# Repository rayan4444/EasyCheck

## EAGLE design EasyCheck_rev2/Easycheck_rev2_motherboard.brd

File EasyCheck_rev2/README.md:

# Easy Check rev 2
## Overview
This version includes bug fixes from the previous iteration and is designed to fit in the prototype, made for HAX Xi'an Demo Day 2019. The design has 4 boards:
* A motherboard: power circuit, MCU (ATSAMD21G), control for heater, fans and servo.
* A connection board for testing chips: ADC, chip connectors
* An Interface board: LCD screen, buzzer, 4 buttons, power LED
* Test chip boards: Serial number IC, contacts for sensing paper, power LED, NTC (temperature sensing)

## Programming
To set up the programming environment, follow the same steps as rev1.

**ATTENTION!**

To run all code properly some modification to the original board definition files from ARDUINO and 3rd party libraries are necessary: the modified files are available in this repository in the /Board Definition and /Libraries used folders.

## Errata
- I2C bus: change R11 and R14 from 4.7k to 2.2k
- The design doesn't account for a battery to keep the RTC powered on. Time gets reset to a user specified date and time at every reboot.

**Note**: the 2019/07/12 prototype uses a slightly different version of the PCB with connection errors that have ALREADY BEEN CORRECTED in the files in this repository
## Recommendations for future designs:

###### Hardware:
- To implement stackable drawers system: consider having a small microcontroller on each connection board that handles serial communication with the motherboard through RS485. you can then daisy chain the drawers as you stack them. The microcontroller on the drawer board can also handle reading the ADC and serial numbers.
- Accommodating to new test papers: move the resistor divider to the chip PCB, so you can customize it for new types of sensing papers with different resistances.

- This design uses an 8W heater, which makes the heating up process slow. Use a more powerful heater to get the system to reach 37 degrees faster. However, make sure the current consumption is within the limits of your power supply.
- Data: consider having some sort of connectivity (Wifi/ethernet) to export data and update the RTC clock.

###### Firmware:
- Scaling of the x-axis in the LCD diplay temperature plot according to test duration
- Improve temperature PID controller by tuning Ki, Kp and Kd better
- Consider using hardware SPI for communication to the display screen
- Consider modifying libraries to include only the necessary parts and reduce memory usage

- Improve timing: consider using timer interrupts to have more precise timing and simplify code structure
- Improve memory usage (variables, function structures etc.)

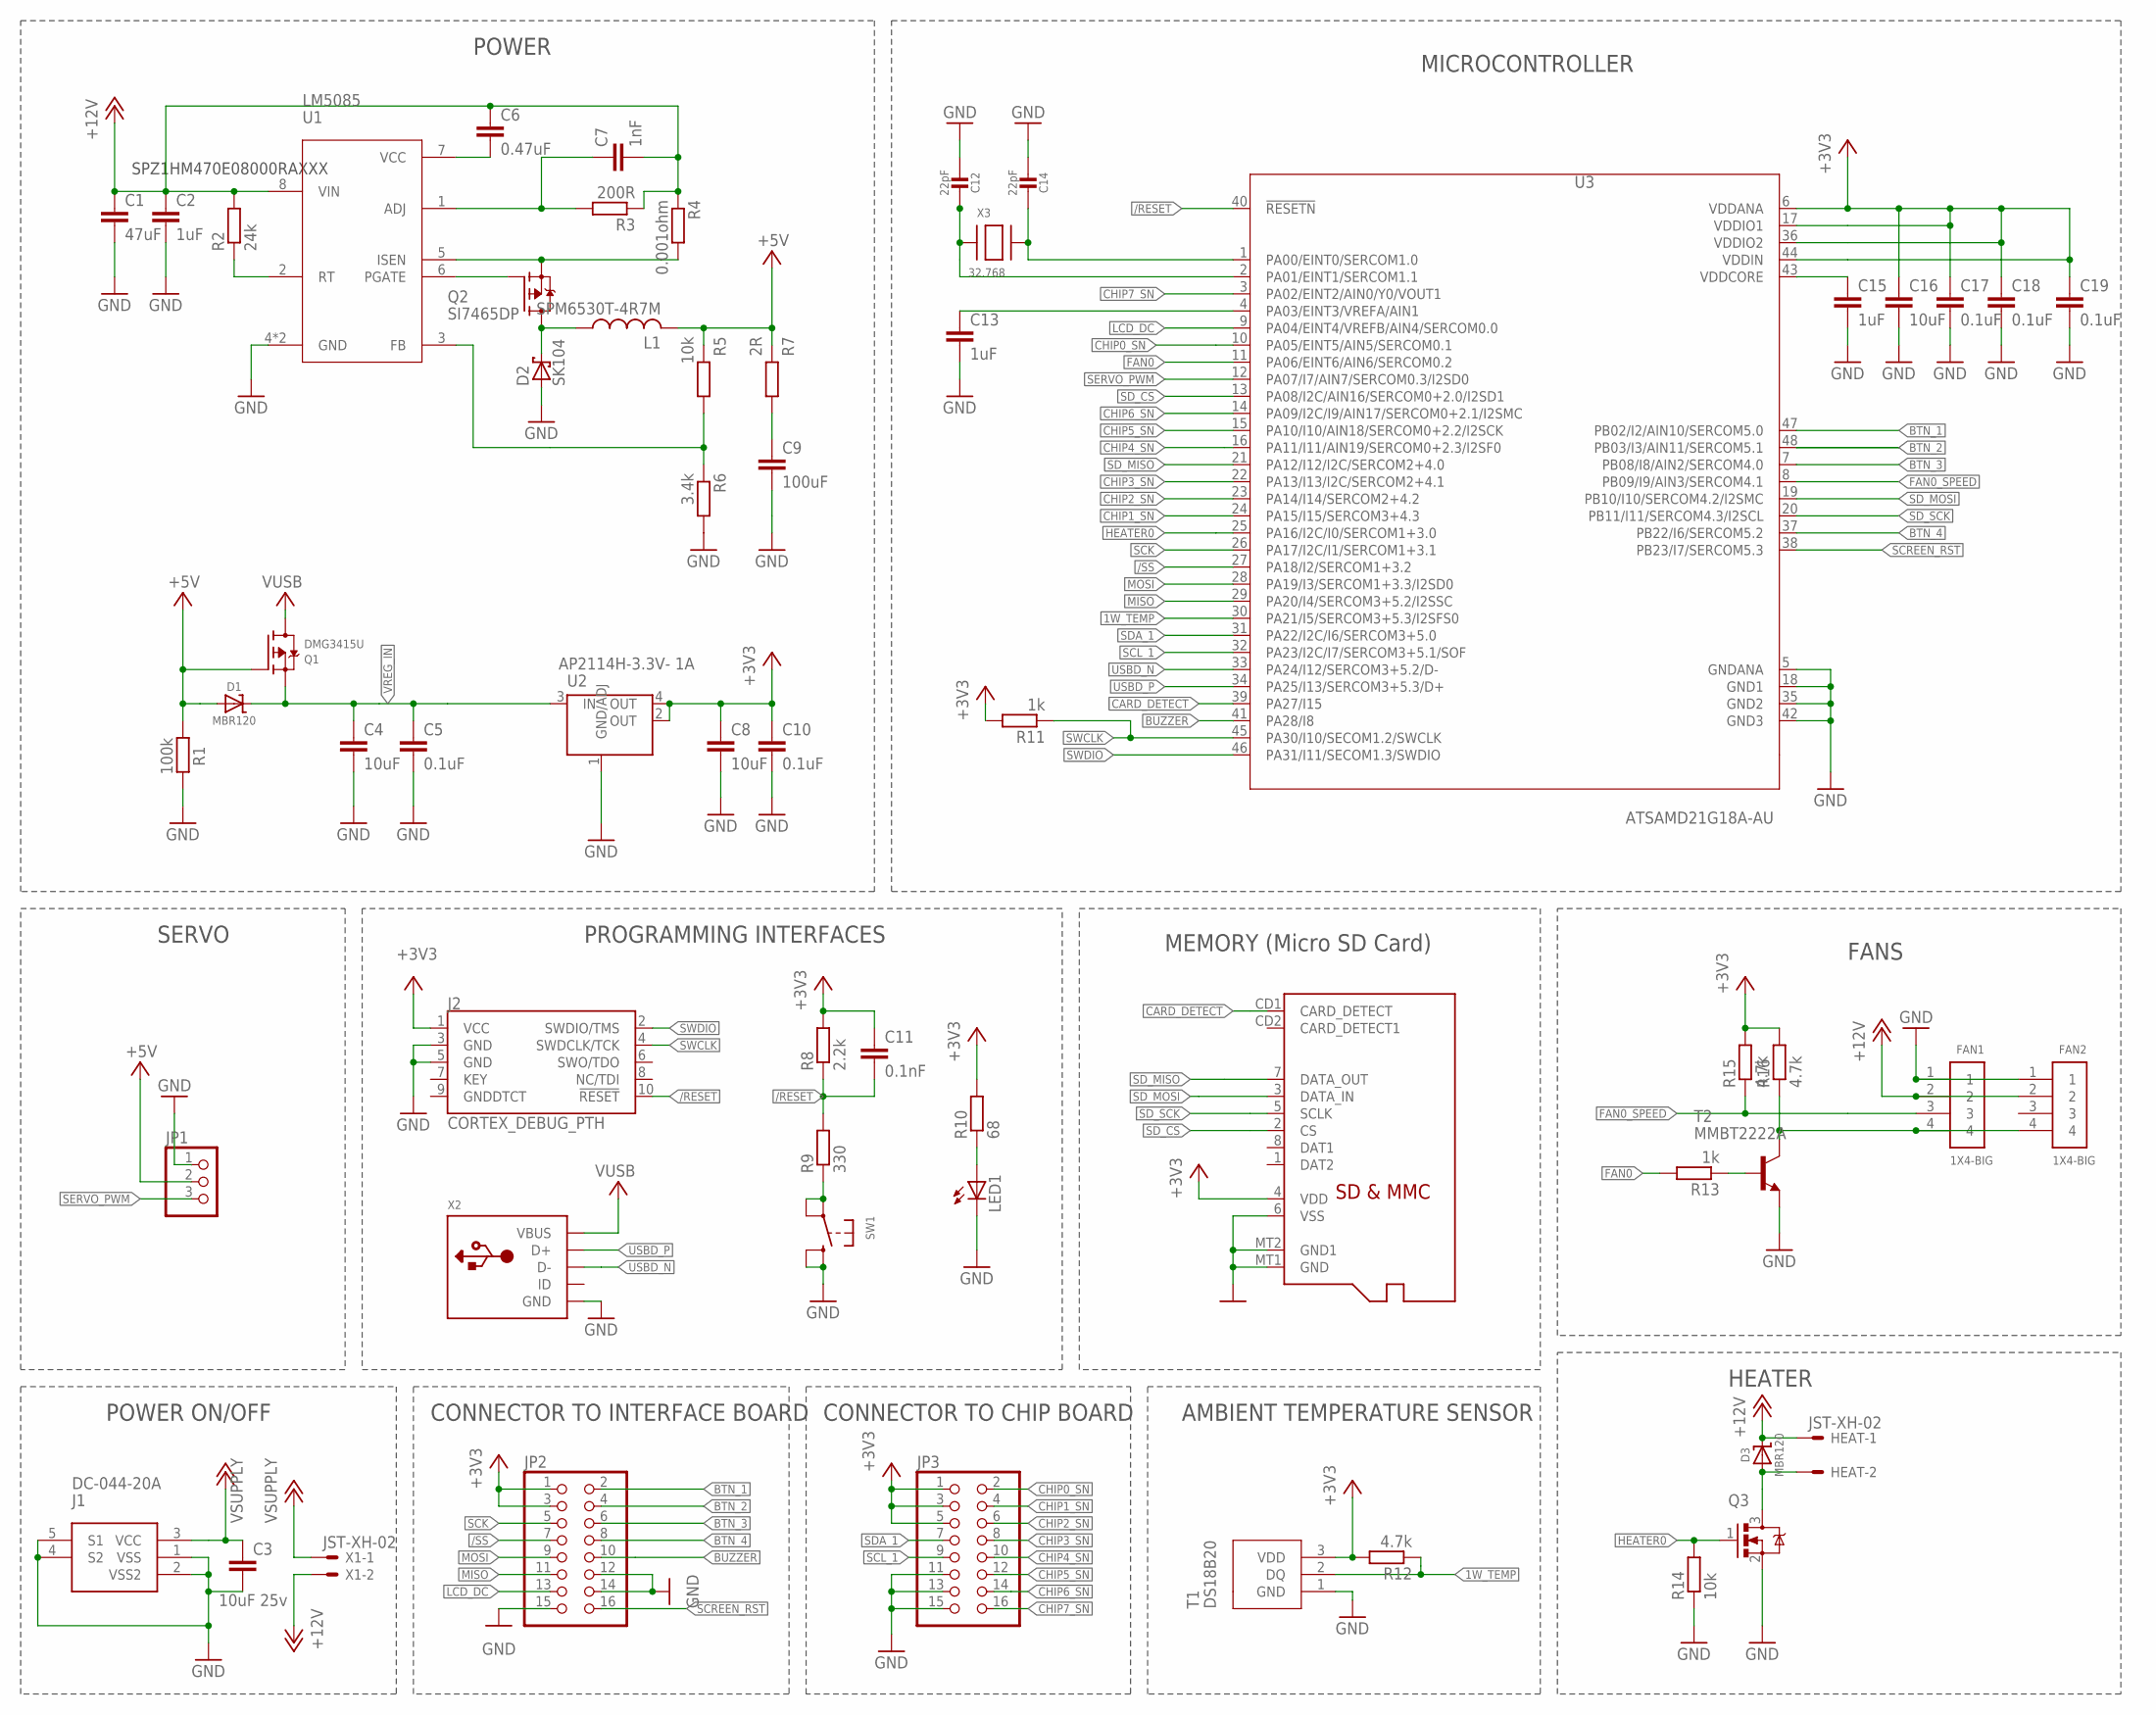
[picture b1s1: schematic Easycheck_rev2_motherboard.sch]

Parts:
C1: 47uF; C1206
C2: 1uF; C1206
C3: 10uF 25v; C1206
C4, C8, C16: 10uF; C0603
C5, C10, C17, C18, C19: 0.1uF; C0603
C6: 0.47uF; C1206
C7: 1nF; C0603
C9: 100uF; C0805
C11: 0.1nF; C0603
C12, C14: 22pF; 0603-NO@1
C13, C15: 1uF; C0603
D1, D3: MBR120; MICROBUILDER_SOD-123
D2: SK104
FAN1, FAN2: 1X4-BIG; 1X04-BIG
HEAT: JST-XH-02; JST-XH-02-PACKAGE-LONG-PAD
J1: DC-044-20A
J2: CORTEX_DEBUG_PTH; 2X5-PTH-1.27MM
JP1: PINHD-1X3; 1X03
JP2, JP3: PINHD-2X8; 2X08
L1: SPM6530T-4R7M
LED1: LEDCHIPLED_0603; CHIPLED_0603
Q1: DMG3415U; SOT23-R
Q2: SI7465DP; SI7465
Q3: DMN6140L; SOT91P240X110-3N
R1: 100k; R0603
R2: 24k; R0603
R3: 200R; R0603
R4: 0.001ohm; R1206
R5, R14: 10k; R0603
R6: 3.4k; R0603
R7: 2R; R0805
R8: 2.2k; R0603
R9: 330; R0603
R10: 68; R0603
R11, R13: 1k; R0603
R12, R15, R16: 4.7k; R0603
SD1: MICROSD
SW1: MICROBUILDER_SWITCH_TACT_SMT_EVQQ2_SMALL; MICROBUILDER_EVQ-Q2_SMALLER
T1: DS18B20; TO92
T2: MMBT2222A; SOT23-BEC
U1: LM5085
U2: AP2114H-3.3V- 1A; GEN_COMP_SOT223
U3: ATSAMD21G18A-AU; QFP50P900X900X120-48N
X1: JST-XH-02; JST-XH-02-PACKAGE-LONG-PAD
X2: MICROBUILDER_USB_MICRO_20329_V2; MICROBUILDER_4UCONN_20329_V2
X3: 32.768; XTAL3215

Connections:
1W_TEMP: R12.1, T1.2 (DQ), U3.30 (PA21/I5/SERCOM3+5.3/I2SFS0)
+3V3: C8.1, C10.1, C11.1, C16.1, C17.1, C18.1, C19.1, J2.1 (VCC), JP2.1, JP2.3, JP3.1, JP3.3, JP3.5, R8.2, R10.2, R11.2, R12.2, R15.2, R16.2, SD1.4 (VDD), T1.3 (VDD), U2.2 (OUT), U2.4 (OUT), U3.6 (VDDANA), U3.17 (VDDIO1), U3.36 (VDDIO2), U3.44 (VDDIN)
+5V: D1.A, JP1.2, L1.2, Q1.1 (G), R1.1, R5.1, R7.1
+12V: C1.1, C2.1, C6.1, C7.2, D3.C, FAN1.2, FAN2.2, HEAT.1, R2.2, R3.1, R4.1, U1.8 (VIN), X1.2
/RESET: C11.2, J2.10 (!RESET), R8.1, R9.2, U3.40 (!RESETN)
/SS: JP2.7, U3.27 (PA18/I2/SERCOM1+3.2)
BTN_1: JP2.2, U3.47 (PB02/I2/AIN10/SERCOM5.0)
BTN_2: JP2.4, U3.48 (PB03/I3/AIN11/SERCOM5.1)
BTN_3: JP2.6, U3.7 (PB08/I8/AIN2/SERCOM4.0)
BTN_4: JP2.8, U3.37 (PB22/I6/SERCOM5.2)
BUZZER: JP2.10, U3.41 (PA28/I8)
CARD_DETECT: SD1.CD1 (CARD_DETECT), U3.39 (PA27/I15)
CHIP0_SN: JP3.2, U3.10 (PA05/EINT5/AIN5/SERCOM0.1)
CHIP1_SN: JP3.4, U3.24 (PA15/I15/SERCOM3+4.3)
CHIP2_SN: JP3.6, U3.23 (PA14/I14/SERCOM2+4.2)
CHIP3_SN: JP3.8, U3.22 (PA13/I13/I2C/SERCOM2+4.1)
CHIP4_SN: JP3.10, U3.16 (PA11/I11/AIN19/SERCOM0+2.3/I2SF0)
CHIP5_SN: JP3.12, U3.15 (PA10/I10/AIN18/SERCOM0+2.2/I2SCK)
CHIP6_SN: JP3.14, U3.14 (PA09/I2C/I9/AIN17/SERCOM0+2.1/I2SMC)
CHIP7_SN: JP3.16, U3.3 (PA02/EINT2/AIN0/Y0/VOUT1)
FAN0: R13.2, U3.11 (PA06/EINT6/AIN6/SERCOM0.2)
FAN0_SPEED: FAN1.3, R15.1, U3.8 (PB09/I9/AIN3/SERCOM4.1)
GND: C1.2, C2.2, C3.2, C4.2, C5.2, C8.2, C9.2, C10.2, C12.2, C13.2, C14.2, C15.2, C16.2, C17.2, C18.2, C19.2, D2.1 (A), FAN1.1, FAN2.1, J1.1 (VSS), J1.2 (VSS2), J1.4 (S2), J1.5 (S1), J2.3 (GND), J2.5 (GND), JP1.1, JP2.12, JP2.14, JP2.15, JP3.11, JP3.13, JP3.15, LED1.C, Q3.2, R1.2, R6.2, R14.1, SD1.6 (VSS), SD1.MT1 (GND), SD1.MT2 (GND1), SW1.B (S), SW1.B' (S1), T1.1 (GND), T2.E, U1.4 (GND), U1.9 (GND), U2.1 (GND/ADJ), U3.5 (GNDANA), U3.18 (GND1), U3.35 (GND2), U3.42 (GND3), X2.BASE@1 (GND), X2.BASE@2 (GND), X2.GND, X2.SPRT@1 (GND), X2.SPRT@2 (GND), X2.SPRT@3 (GND), X2.SPRT@4 (GND)
HEATER0: Q3.1, R14.2, U3.25 (PA16/I2C/I0/SERCOM1+3.0)
LCD_DC: JP2.13, U3.9 (PA04/EINT4/VREFB/AIN4/SERCOM0.0)
MISO: JP2.11, U3.29 (PA20/I4/SERCOM3+5.2/I2SSC)
MOSI: JP2.9, U3.28 (PA19/I3/SERCOM1+3.3/I2SD0)
unnamed: C9.1, R7.2
unnamed: FAN1.4, FAN2.4, R16.1, T2.C
unnamed: R13.1, T2.B
unnamed: D3.A, HEAT.2, Q3.3
unnamed: R9.1, SW1.A, SW1.A' (P1)
unnamed: C12.1, U3.2 (PA01/EINT1/SERCOM1.1), X3.P$1
unnamed: C14.1, U3.1 (PA00/EINT0/SERCOM1.0), X3.P$2
unnamed: C13.1, U3.4 (PA03/EINT3/VREFA/AIN1)
unnamed: C15.1, U3.43 (VDDCORE)
unnamed: LED1.A, R10.1
unnamed: R2.1, U1.2 (RT)
unnamed: Q2.1 (S), Q2.2 (S), Q2.3 (S), R4.2, U1.5 (ISEN)
unnamed: C7.1, R3.2, U1.1 (ADJ)
unnamed: R5.2, R6.1, U1.3 (FB)
unnamed: C6.2, U1.7 (VCC)
unnamed: D2.2 (C), L1.1, Q2.5 (D), Q2.6 (D), Q2.7 (D), Q2.8 (D), Q2.9 (D)
unnamed: Q2.4 (G), U1.6 (PGATE)
SCK: JP2.5, U3.26 (PA17/I2C/I1/SERCOM1+3.1)
SCL_1: JP3.9, U3.32 (PA23/I2C/I7/SERCOM3+5.1/SOF)
SCREEN_RST: JP2.16, U3.38 (PB23/I7/SERCOM5.3)
SDA_1: JP3.7, U3.31 (PA22/I2C/I6/SERCOM3+5.0)
SD_CS: SD1.2 (CS), U3.13 (PA08/I2C/AIN16/SERCOM0+2.0/I2SD1)
SD_MISO: SD1.7 (DATA_OUT), U3.21 (PA12/I12/I2C/SERCOM2+4.0)
SD_MOSI: SD1.3 (DATA_IN), U3.19 (PB10/I10/SERCOM4.2/I2SMC)
SD_SCK: SD1.5 (SCLK), U3.20 (PB11/I11/SERCOM4.3/I2SCL)
SERVO_PWM: JP1.3, U3.12 (PA07/I7/AIN7/SERCOM0.3/I2SD0)
SWCLK: J2.4 (SWDCLK/TCK), R11.1, U3.45 (PA30/I10/SECOM1.2/SWCLK)
SWDIO: J2.2 (SWDIO/TMS), U3.46 (PA31/I11/SECOM1.3/SWDIO)
USBD_N: U3.33 (PA24/I12/SERCOM3+5.2/D-), X2.D-
USBD_P: U3.34 (PA25/I13/SERCOM3+5.3/D+), X2.D+
VREG_IN: C4.1, C5.1, D1.C, Q1.2 (S), U2.3 (IN)
VSUPPLY: C3.1, J1.3 (VCC), X1.1
VUSB: Q1.3 (D), X2.VBUS

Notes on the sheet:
POWER
SPZ1HM470E08000RAXXX
MICROCONTROLLER
MEMORY (Micro SD Card)
PROGRAMMING INTERFACES
AMBIENT TEMPERATURE SENSOR
FANS
HEATER
POWER ON/OFF
CONNECTOR TO INTERFACE BOARD
CONNECTOR TO CHIP BOARD
SERVO

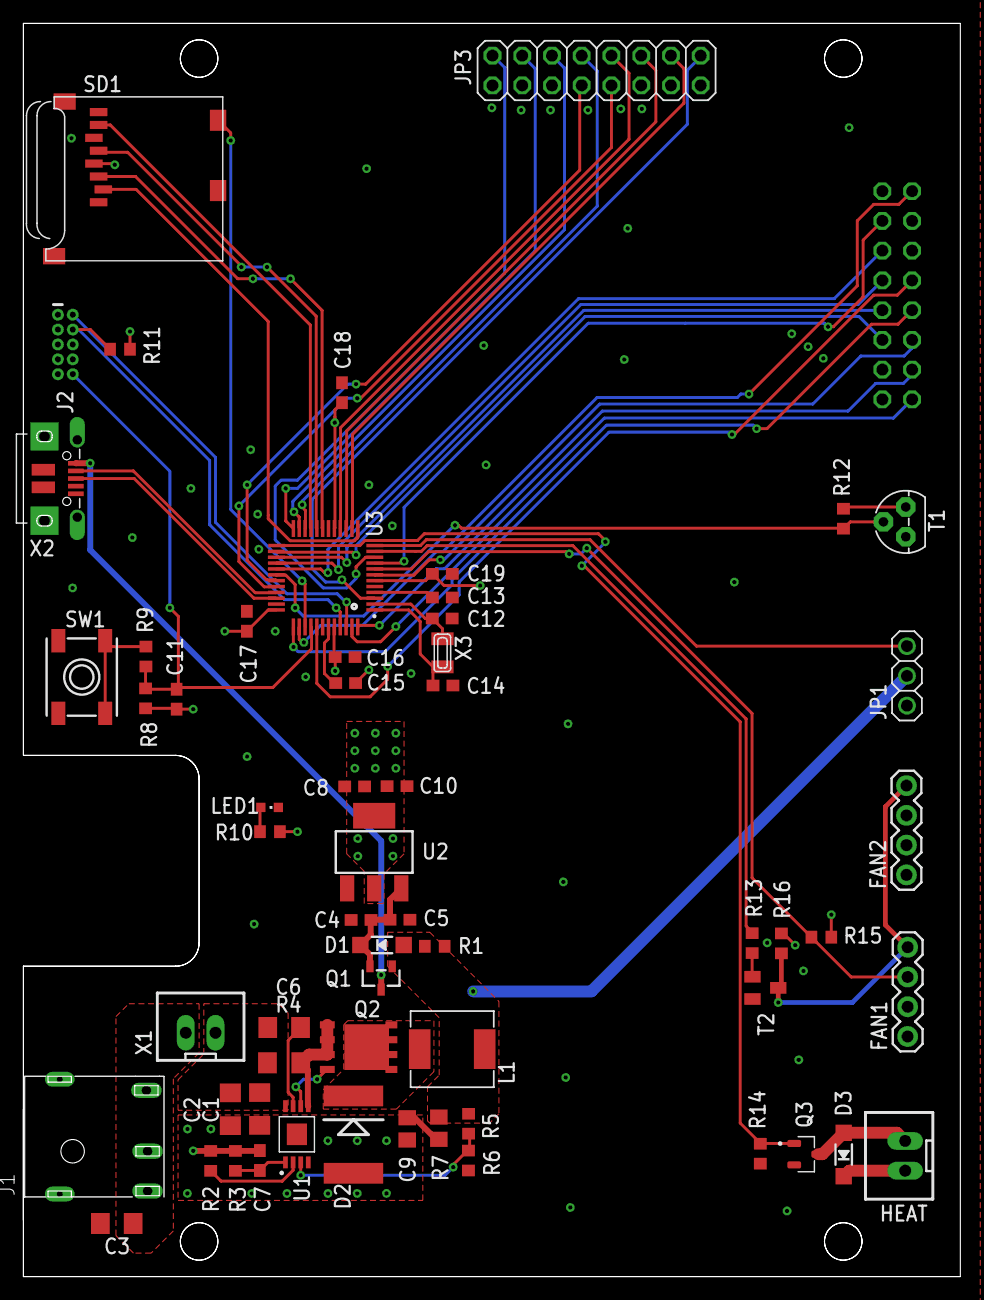
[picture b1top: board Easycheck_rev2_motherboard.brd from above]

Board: 4 copper layers, 80.0 x 107.0 mm, 61 parts (1 on the bottom side), 60 nets.

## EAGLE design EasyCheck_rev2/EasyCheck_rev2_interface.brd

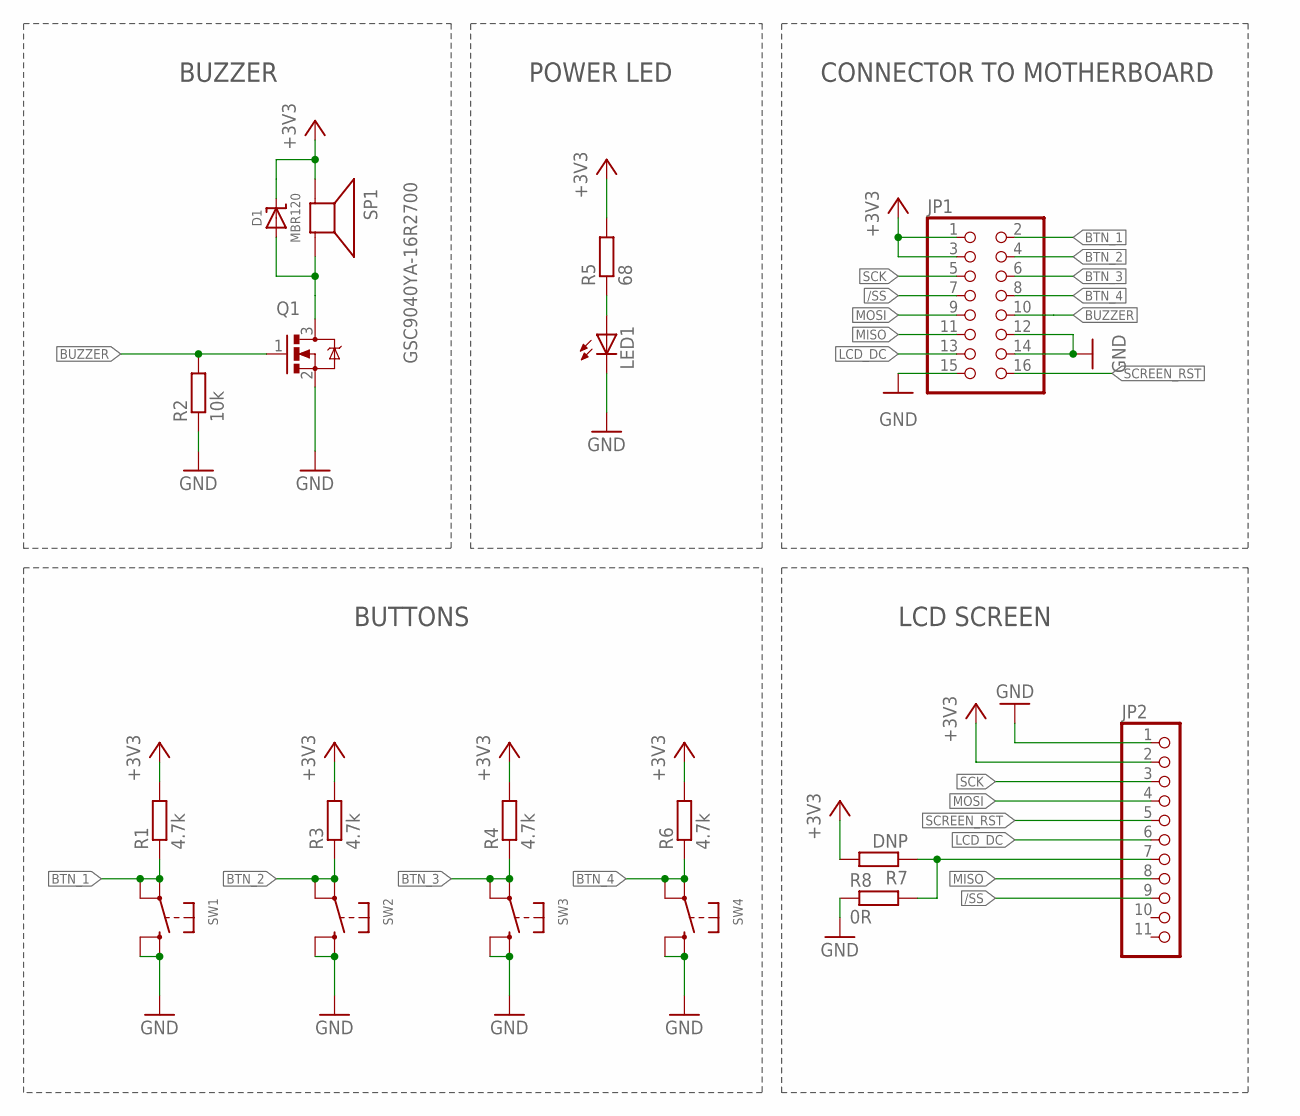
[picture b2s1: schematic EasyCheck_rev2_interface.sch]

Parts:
D1: MBR120; MICROBUILDER_SOD-123
JP1: PINHD-2X8; 2X08
JP2: PINHD-1X11; 1X11
LED1: LEDCHIPLED_0603; CHIPLED_0603
Q1: DMN6140L; SOT91P240X110-3N
R1, R3, R4, R6: 4.7k; R0603
R2: 10k; R0603
R5: 68; R0603
R7: DNP; R0603
R8: 0R; R0603
SP1: GSC9040YA-16R2700
SW1, SW2, SW3, SW4: MICROBUILDER_SWITCH_TACT_SMT_EVQQ2_SMALL; MICROBUILDER_EVQ-Q2_SMALLER

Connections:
+3V3: D1.C, JP1.1, JP1.3, JP2.2, R1.2, R3.2, R4.2, R5.2, R6.2, R7.2, SP1.P$3 (+)
/SS: JP1.7, JP2.9
BTN_1: JP1.2, R1.1, SW1.A, SW1.A' (P1)
BTN_2: JP1.4, R3.1, SW2.A, SW2.A' (P1)
BTN_3: JP1.6, R4.1, SW3.A, SW3.A' (P1)
BTN_4: JP1.8, R6.1, SW4.A, SW4.A' (P1)
BUZZER: JP1.10, Q1.1, R2.2
GND: JP1.12, JP1.14, JP1.15, JP2.1, LED1.C, Q1.2, R2.1, R8.1, SW1.B (S), SW1.B' (S1), SW2.B (S), SW2.B' (S1), SW3.B (S), SW3.B' (S1), SW4.B (S), SW4.B' (S1)
LCD_DC: JP1.13, JP2.6
MISO: JP1.11, JP2.8
MOSI: JP1.9, JP2.4
unnamed: JP2.7, R7.1, R8.2
unnamed: D1.A, Q1.3, SP1.P$2 (-)
unnamed: LED1.A, R5.1
SCK: JP1.5, JP2.3
SCREEN_RST: JP1.16, JP2.5

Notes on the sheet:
BUZZER
CONNECTOR TO MOTHERBOARD
BUTTONS
LCD SCREEN
POWER LED

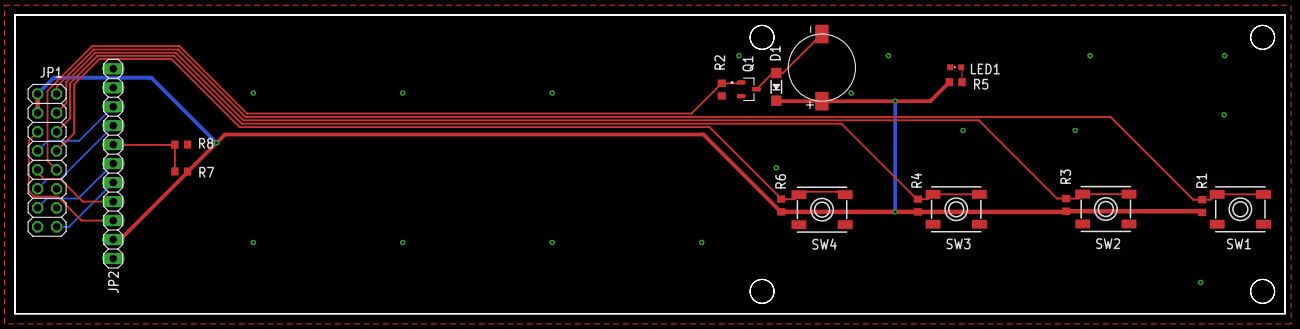
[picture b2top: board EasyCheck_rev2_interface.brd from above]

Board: 2 copper layers, 170.0 x 40.0 mm, 18 parts (0 on the bottom side), 16 nets.

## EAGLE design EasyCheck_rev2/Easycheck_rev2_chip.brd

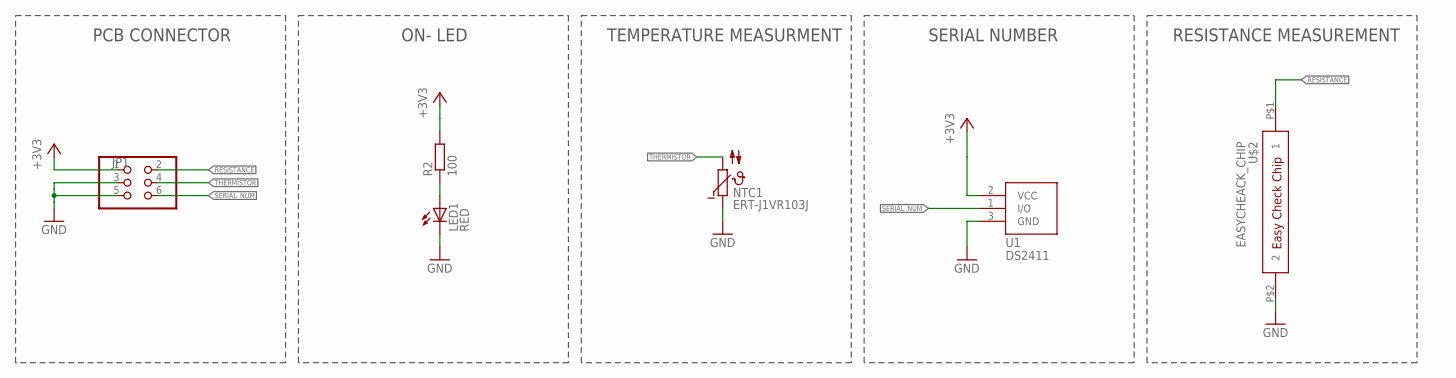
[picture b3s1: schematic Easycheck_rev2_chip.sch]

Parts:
JP1: PINHD-2X3; 2X03
LED1: RED; CHIPLED_0603
NTC1: ERT-J1VR103J; C0603K
R2: 100; R0402
U1: DS2411; SOT23
U$2: EASYCHEACK_CHIP; EASYCHECK_CHIP

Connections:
+3V3: JP1.1, R2.2, U1.2 (VCC)
GND: JP1.3, JP1.5, LED1.C, NTC1.1, U1.3 (GND), U$2.P$2 (2)
unnamed: LED1.A, R2.1
RESISTANCE: JP1.2, U$2.P$1 (1)
SERIAL_NUM: JP1.6, U1.1 (I/O)
THERMISTOR: JP1.4, NTC1.2

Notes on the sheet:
TEMPERATURE MEASURMENT
RESISTANCE MEASUREMENT
SERIAL NUMBER
PCB CONNECTOR
ON- LED

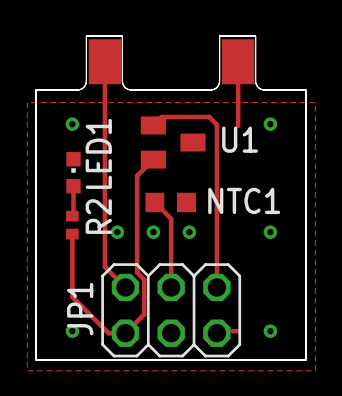
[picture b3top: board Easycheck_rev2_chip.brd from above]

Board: 2 copper layers, 15.0 x 18.0 mm, 6 parts (0 on the bottom side), 6 nets.

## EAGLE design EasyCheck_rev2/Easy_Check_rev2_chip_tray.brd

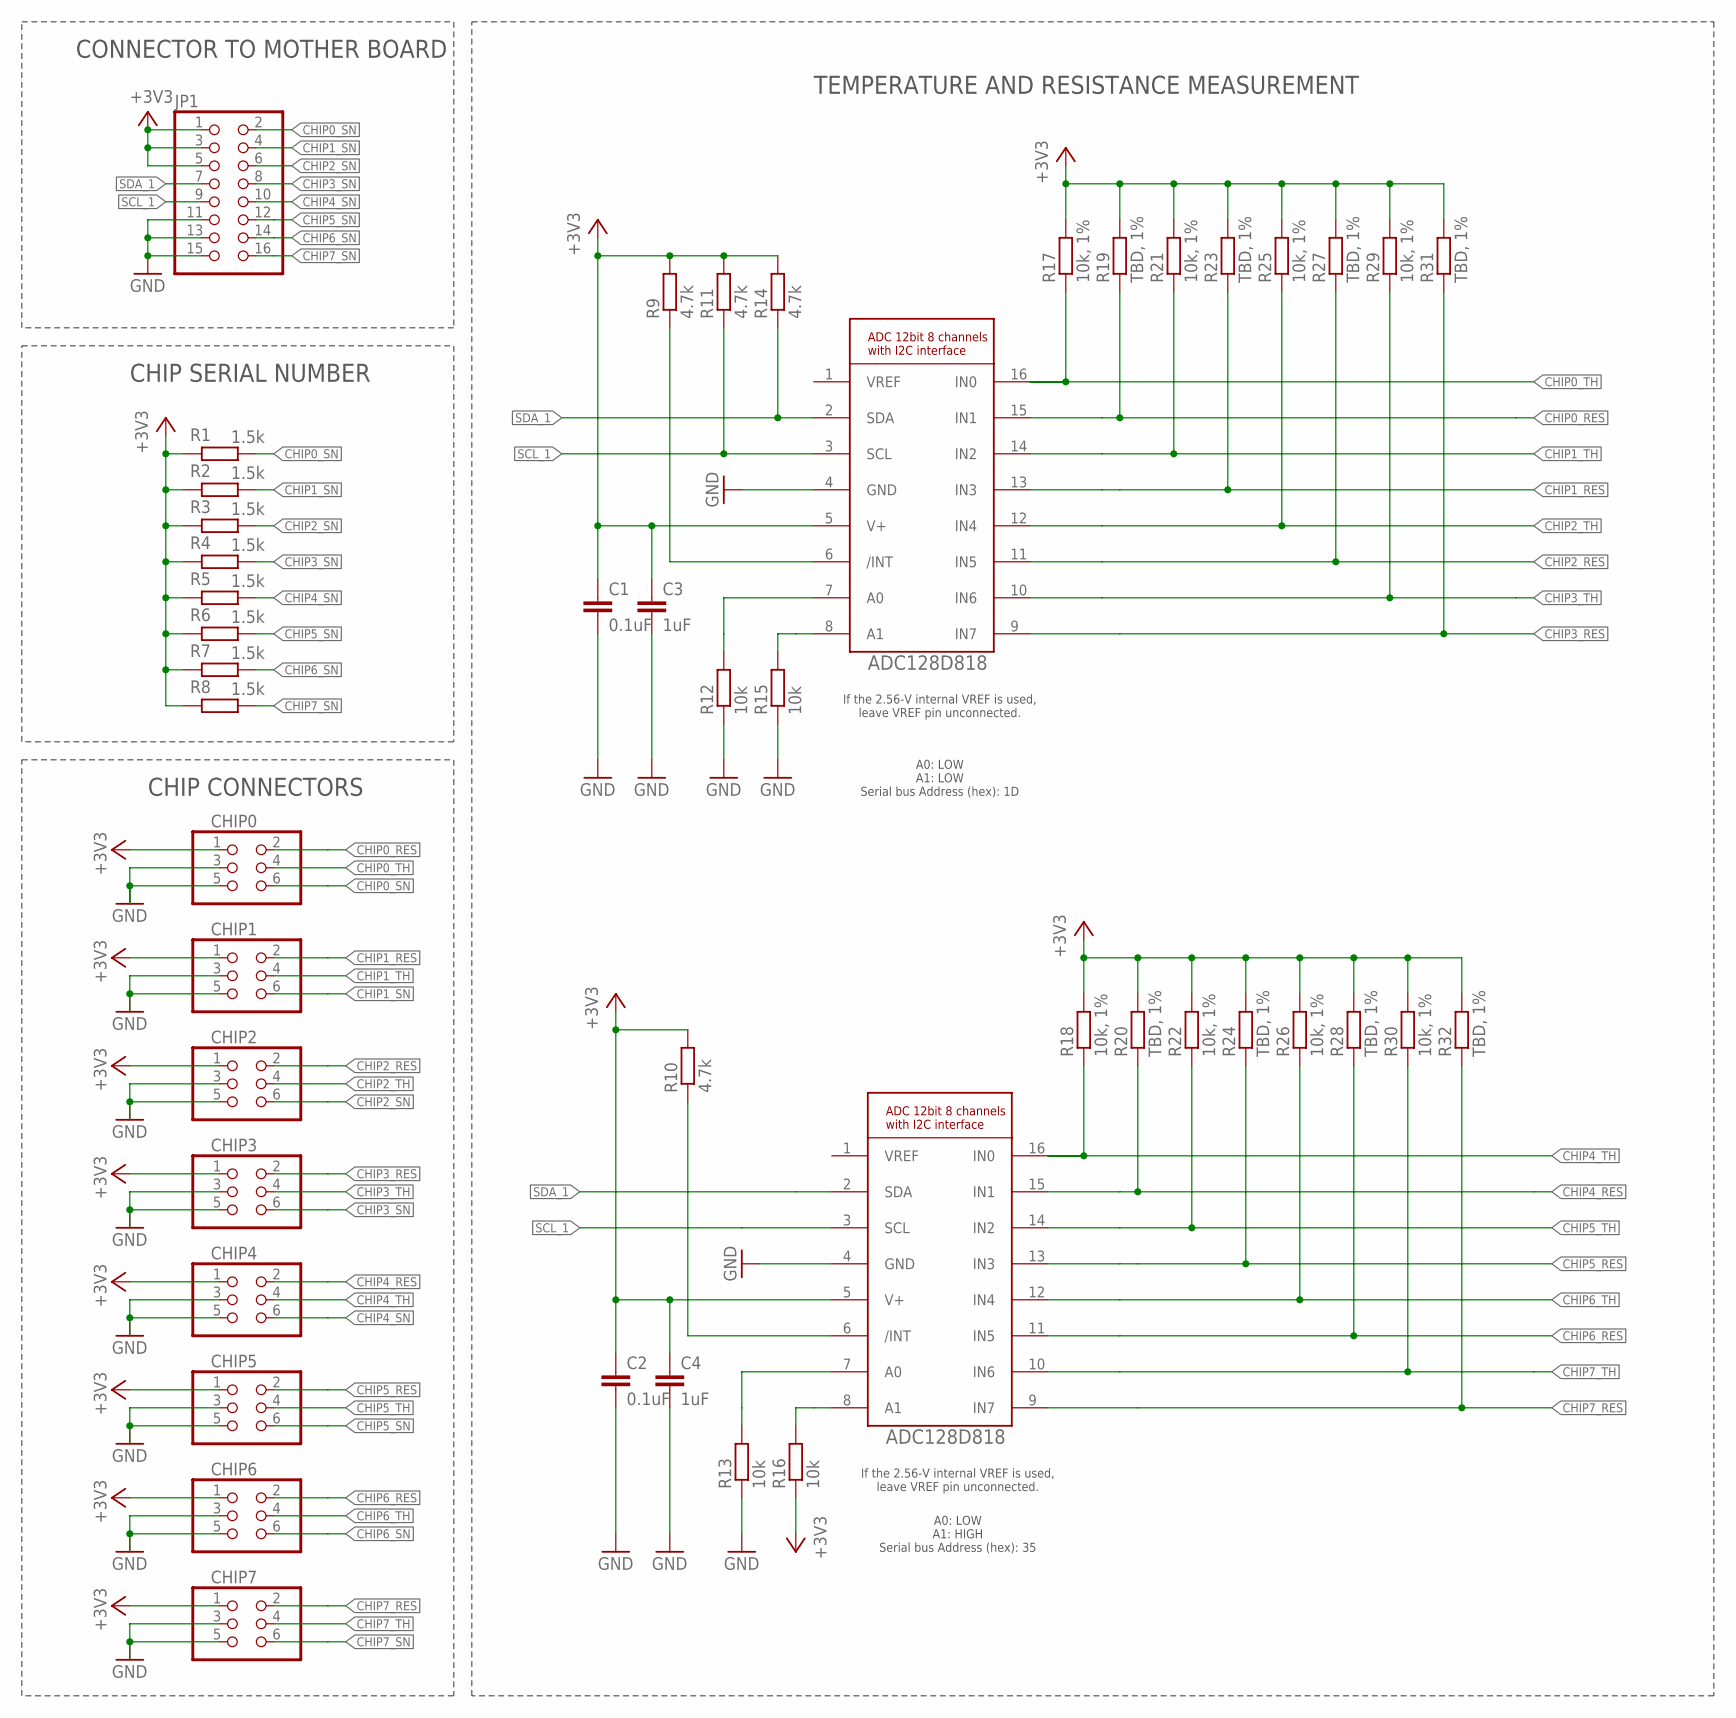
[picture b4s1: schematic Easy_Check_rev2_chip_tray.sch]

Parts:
C1, C2: 0.1uF; C0603
C3, C4: 1uF; C0603
CHIP0, CHIP1, CHIP2, CHIP3, CHIP4, CHIP5, CHIP6, CHIP7: PINHD-2X3; 2X03
JP1: PINHD-2X8; 2X08
R1, R2, R3, R4, R5, R6, R7, R8: 1.5k; R0603
R9, R10, R11, R14: 4.7k; R0603
R12, R13, R15, R16: 10k; R0603
R17, R18, R21, R22, R25, R26, R29, R30: 10k, 1%; R0603
R19, R20, R23, R24, R27, R28, R31, R32: TBD, 1%; R0603
U1, U2: LMD128D818; ADC128D818

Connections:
+3V3: C1.1, C2.1, C3.1, C4.1, CHIP0.1, CHIP1.1, CHIP2.1, CHIP3.1, CHIP4.1, CHIP5.1, CHIP6.1, CHIP7.1, JP1.1, JP1.3, JP1.5, R1.2, R2.2, R3.2, R4.2, R5.2, R6.2, R7.2, R8.2, R9.2, R10.2, R11.2, R14.2, R16.1, R17.2, R18.2, R19.2, R20.2, R21.2, R22.2, R23.2, R24.2, R25.2, R26.2, R27.2, R28.2, R29.2, R30.2, R31.2, R32.2, U1.5 (V+), U2.5 (V+)
CHIP0_RES: CHIP0.2, R19.1, U1.15 (IN1)
CHIP0_SN: CHIP0.6, JP1.2, R1.1
CHIP0_TH: CHIP0.4, R17.1, U1.16 (IN0)
CHIP1_RES: CHIP1.2, R23.1, U1.13 (IN3)
CHIP1_SN: CHIP1.6, JP1.4, R2.1
CHIP1_TH: CHIP1.4, R21.1, U1.14 (IN2)
CHIP2_RES: CHIP2.2, R27.1, U1.11 (IN5)
CHIP2_SN: CHIP2.6, JP1.6, R3.1
CHIP2_TH: CHIP2.4, R25.1, U1.12 (IN4)
CHIP3_RES: CHIP3.2, R31.1, U1.9 (IN7)
CHIP3_SN: CHIP3.6, JP1.8, R4.1
CHIP3_TH: CHIP3.4, R29.1, U1.10 (IN6)
CHIP4_RES: CHIP4.2, R20.1, U2.15 (IN1)
CHIP4_SN: CHIP4.6, JP1.10, R5.1
CHIP4_TH: CHIP4.4, R18.1, U2.16 (IN0)
CHIP5_RES: CHIP5.2, R24.1, U2.13 (IN3)
CHIP5_SN: CHIP5.6, JP1.12, R6.1
CHIP5_TH: CHIP5.4, R22.1, U2.14 (IN2)
CHIP6_RES: CHIP6.2, R28.1, U2.11 (IN5)
CHIP6_SN: CHIP6.6, JP1.14, R7.1
CHIP6_TH: CHIP6.4, R26.1, U2.12 (IN4)
CHIP7_RES: CHIP7.2, R32.1, U2.9 (IN7)
CHIP7_SN: CHIP7.6, JP1.16, R8.1
CHIP7_TH: CHIP7.4, R30.1, U2.10 (IN6)
GND: C1.2, C2.2, C3.2, C4.2, CHIP0.3, CHIP0.5, CHIP1.3, CHIP1.5, CHIP2.3, CHIP2.5, CHIP3.3, CHIP3.5, CHIP4.3, CHIP4.5, CHIP5.3, CHIP5.5, CHIP6.3, CHIP6.5, CHIP7.3, CHIP7.5, JP1.11, JP1.13, JP1.15, R12.1, R13.1, R15.1, U1.4 (GND), U2.4 (GND)
unnamed: R9.1, U1.6 (/INT)
unnamed: R10.1, U2.6 (/INT)
unnamed: R12.2, U1.7 (A0)
unnamed: R15.2, U1.8 (A1)
unnamed: R13.2, U2.7 (A0)
unnamed: R16.2, U2.8 (A1)
SCL_1: JP1.9, R11.1, U1.3 (SCL), U2.3 (SCL)
SDA_1: JP1.7, R14.1, U1.2 (SDA), U2.2 (SDA)

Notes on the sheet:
CONNECTOR TO MOTHER BOARD
TEMPERATURE AND RESISTANCE MEASUREMENT
A0: LOW A1: LOW Serial bus Address (hex): 1D
A0: LOW A1: HIGH Serial bus Address (hex): 35
If the 2.56-V internal VREF is used, leave VREF pin unconnected.
CHIP SERIAL NUMBER
CHIP CONNECTORS

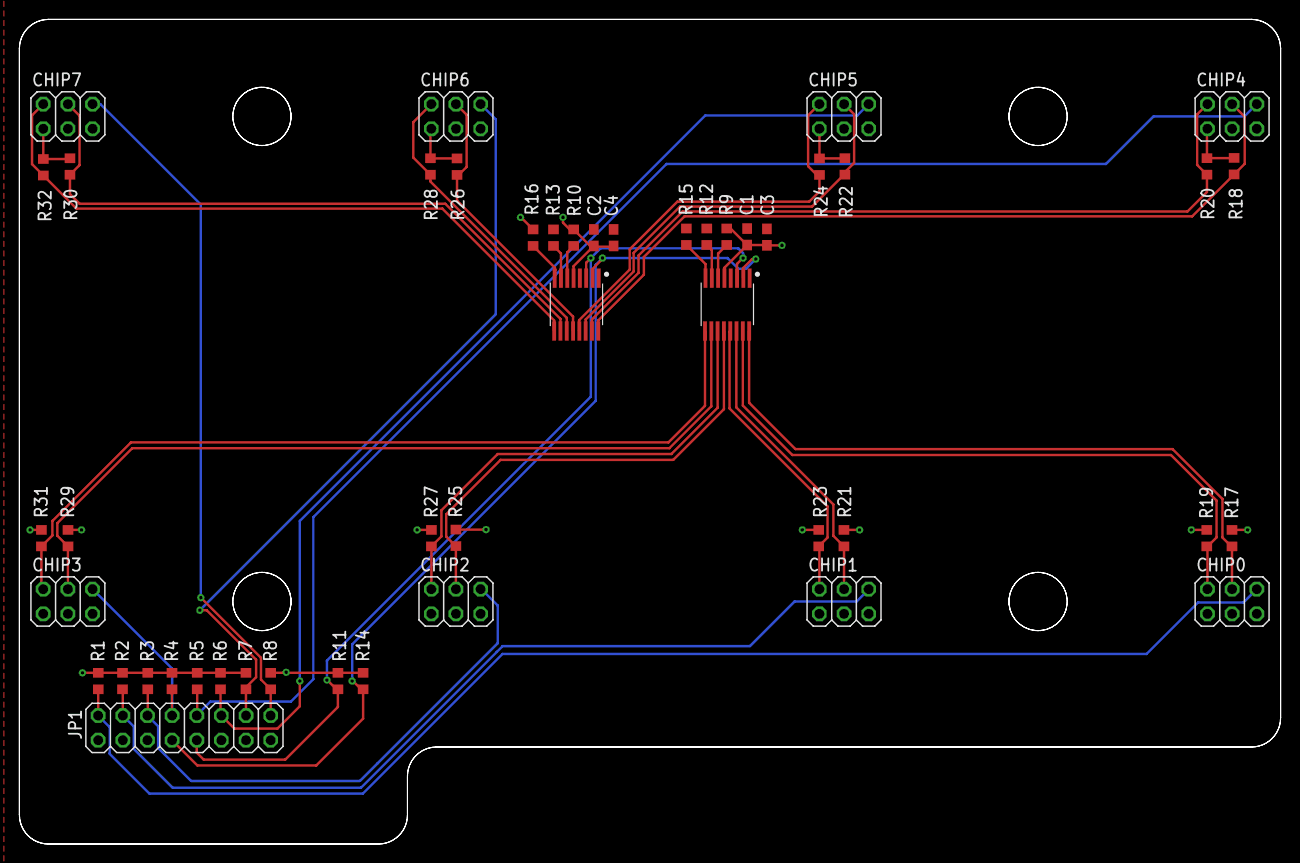
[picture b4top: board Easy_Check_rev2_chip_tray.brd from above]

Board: 2 copper layers, 130.0 x 85.0 mm, 47 parts (0 on the bottom side), 34 nets.

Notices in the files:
Board Definition/variant.cpp:
Copyright (c) 2014-2015 Arduino LLC.  All right reserved.
parts and their libraries:
microbuilder: This work is placed in the public domain, and may be freely used for commercial and non-commercial work with the following conditions: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
SparkFun-Connectors: Licensing: Creative Commons ShareAlike 4.0 International - https://creativecommons.org/licenses/by-sa/4.0
